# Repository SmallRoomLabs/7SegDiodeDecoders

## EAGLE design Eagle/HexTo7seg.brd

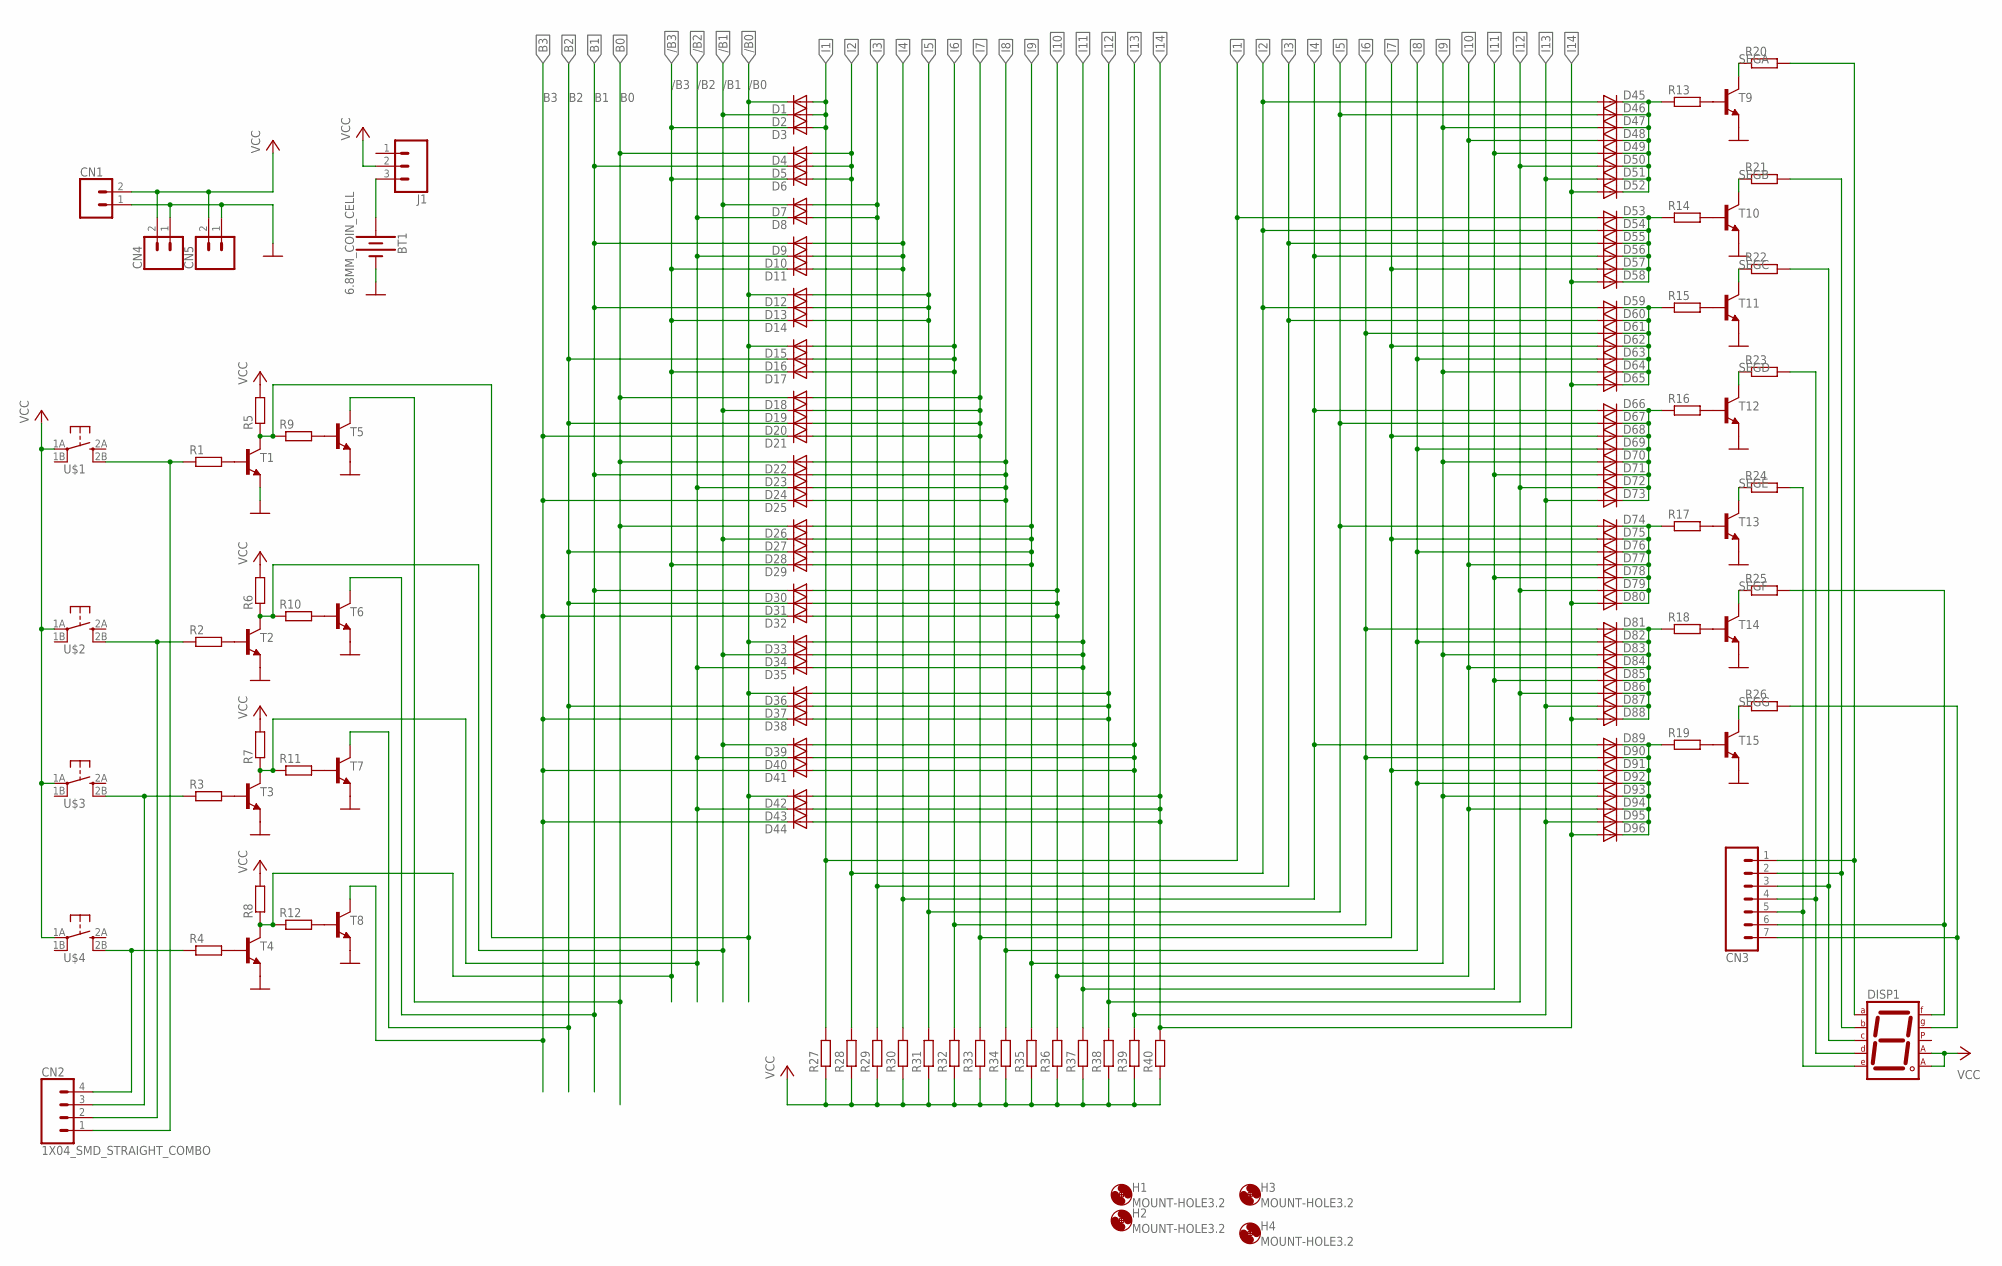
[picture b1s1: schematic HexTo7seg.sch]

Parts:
BT1: 6.8MM_COIN_CELL; BATTCOM_20MM_PTH
CN1, CN4, CN5: CONN_02; 1X02
CN2: 1X04_SMD_STRAIGHT_COMBO; 1X04
CN3: CONN_07; 1X07
D1, D2, D3, D4, D5, D6, D7, D8, D9, D10, D11, D12, D13, D14, D15, D16, D17, D18, D19, D20, D21, D22, D23, D24, D25, D26, D27, D28, D29, D30, D31, D32, D33, D34, D35, D36, D37, D38, D39, D40, D41, D42, D43, D44, D45, D46, D47, D48, D49, D50, D51, D52, D53, D54, D55, D56, D57, D58, D59, D60, D61, D62, D63, D64, D65, D66, D67, D68, D69, D70, D71, D72, D73, D74, D75, D76, D77, D78, D79, D80, D81, D82, D83, D84, D85, D86, D87, D88, D89, D90, D91, D92, D93, D94, D95, D96: SMALL_DIODEDO35-7; DO35-7
DISP1: 7SEG-CA; 7SEG-13
H1, H2, H3, H4: MOUNT-HOLE3.2; 3,2
J1: CONN_03NP; 1X03NOSTOP
R1, R2, R3, R4, R5, R6, R7, R8, R9, R10, R11, R12, R13, R14, R15, R16, R17, R18, R19, R20, R21, R22, R23, R24, R25, R26, R27, R28, R29, R30, R31, R32, R33, R34, R35, R36, R37, R38, R39, R40: RESISTOR7MM; 7MM_RESISTOR
T1, T2, T3, T4, T5, T6, T7, T8, T9, T10, T11, T12, T13, T14, T15: BC547B-NPN-TO92-CBE; TO92-CBE
U$1, U$2, U$3, U$4: TACTILETACT-6X6-PTH; TACTILE-PTH

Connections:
/B0: D1.C, D12.C, D15.C, D33.C, D36.C, D42.C, R5.1, R9.1, T1.C
/B1: D2.C, D7.C, D19.C, D27.C, D34.C, D39.C, R6.1, R10.1, T2.C
/B2: D8.C, D10.C, D24.C, D35.C, D40.C, D43.C, R7.1, R11.1, T3.C
/B3: D3.C, D6.C, D11.C, D14.C, D17.C, D29.C, R8.1, R12.1, T4.C
B0: D4.C, D18.C, D22.C, D26.C, T5.C
B1: D5.C, D9.C, D13.C, D23.C, D30.C, T6.C
B2: D16.C, D20.C, D28.C, D31.C, D37.C, T7.C
B3: D21.C, D25.C, D32.C, D38.C, D41.C, D44.C, T8.C
GND: BT1.2 (-), CN1.1, CN4.1, CN5.1, T1.E, T2.E, T3.E, T4.E, T5.E, T6.E, T7.E, T8.E, T9.E, T10.E, T11.E, T12.E, T13.E, T14.E, T15.E
I1: D1.A, D2.A, D3.A, D53.A, R27.2
I2: D4.A, D5.A, D6.A, D45.A, D54.A, D59.A, R28.2
I3: D7.A, D8.A, D55.A, D60.A, R29.2
I4: D9.A, D10.A, D11.A, D56.A, D66.A, D89.A, R30.2
I5: D12.A, D13.A, D14.A, D46.A, D67.A, D74.A, R31.2
I6: D15.A, D16.A, D17.A, D61.A, D81.A, D90.A, R32.2
I7: D18.A, D19.A, D20.A, D21.A, D57.A, D62.A, D68.A, D75.A, D91.A, R33.2
I8: D22.A, D23.A, D24.A, D25.A, D63.A, D69.A, D76.A, D82.A, D92.A, R34.2
I9: D26.A, D27.A, D28.A, D29.A, D47.A, D64.A, D70.A, D83.A, D93.A, R35.2
I10: D30.A, D31.A, D32.A, D48.A, D77.A, D84.A, D94.A, R36.2
I11: D33.A, D34.A, D35.A, D49.A, D71.A, D78.A, D85.A, R37.2
I12: D36.A, D37.A, D38.A, D50.A, D72.A, D79.A, D86.A, R38.2
I13: D39.A, D40.A, D41.A, D51.A, D73.A, D87.A, D95.A, R39.2
I14: D42.A, D43.A, D44.A, D52.A, D58.A, D65.A, D80.A, D88.A, D96.A, R40.2
IN0: CN2.1, R1.1, U$1.2B
IN1: CN2.2, R2.1, U$2.2B
IN2: CN2.3, R3.1, U$3.2B
IN3: CN2.4, R4.1, U$4.2B
unnamed: R13.2, T9.B
unnamed: CN3.1, DISP1.7 (A), R20.2
unnamed: R14.2, T10.B
unnamed: R15.2, T11.B
unnamed: R16.2, T12.B
unnamed: R17.2, T13.B
unnamed: R18.2, T14.B
unnamed: R19.2, T15.B
unnamed: CN3.2, DISP1.6 (B), R21.2
unnamed: CN3.3, DISP1.4 (C), R22.2
unnamed: CN3.4, DISP1.2 (D), R23.2
unnamed: CN3.5, DISP1.1 (E), R24.2
unnamed: CN3.6, DISP1.9 (F), R25.2
unnamed: CN3.7, DISP1.10 (G), R26.2
unnamed: BT1.1 (+), J1.3
unnamed: R1.2, T1.B
unnamed: R2.2, T2.B
unnamed: R3.2, T3.B
unnamed: R4.2, T4.B
unnamed: R12.2, T8.B
unnamed: R11.2, T7.B
unnamed: R10.2, T6.B
unnamed: R9.2, T5.B
ORA: D45.C, D46.C, D47.C, D48.C, D49.C, D50.C, D51.C, D52.C, R13.1
ORB: D53.C, D54.C, D55.C, D56.C, D57.C, D58.C, R14.1
ORC: D59.C, D60.C, D61.C, D62.C, D63.C, D64.C, D65.C, R15.1
ORD: D66.C, D67.C, D68.C, D69.C, D70.C, D71.C, D72.C, D73.C, R16.1
ORE: D74.C, D75.C, D76.C, D77.C, D78.C, D79.C, D80.C, R17.1
ORF: D81.C, D82.C, D83.C, D84.C, D85.C, D86.C, D87.C, D88.C, R18.1
ORG: D89.C, D90.C, D91.C, D92.C, D93.C, D94.C, D95.C, D96.C, R19.1
SEGA: R20.1, T9.C
SEGB: R21.1, T10.C
SEGC: R22.1, T11.C
SEGD: R23.1, T12.C
SEGE: R24.1, T13.C
SEGF: R25.1, T14.C
SEGG: R26.1, T15.C
VCC: CN1.2, CN4.2, CN5.2, DISP1.3 (CA1), DISP1.8 (CA2), J1.2, R5.2, R6.2, R7.2, R8.2, R27.1, R28.1, R29.1, R30.1, R31.1, R32.1, R33.1, R34.1, R35.1, R36.1, R37.1, R38.1, R39.1, R40.1, U$1.1A, U$2.1A, U$3.1A, U$4.1A

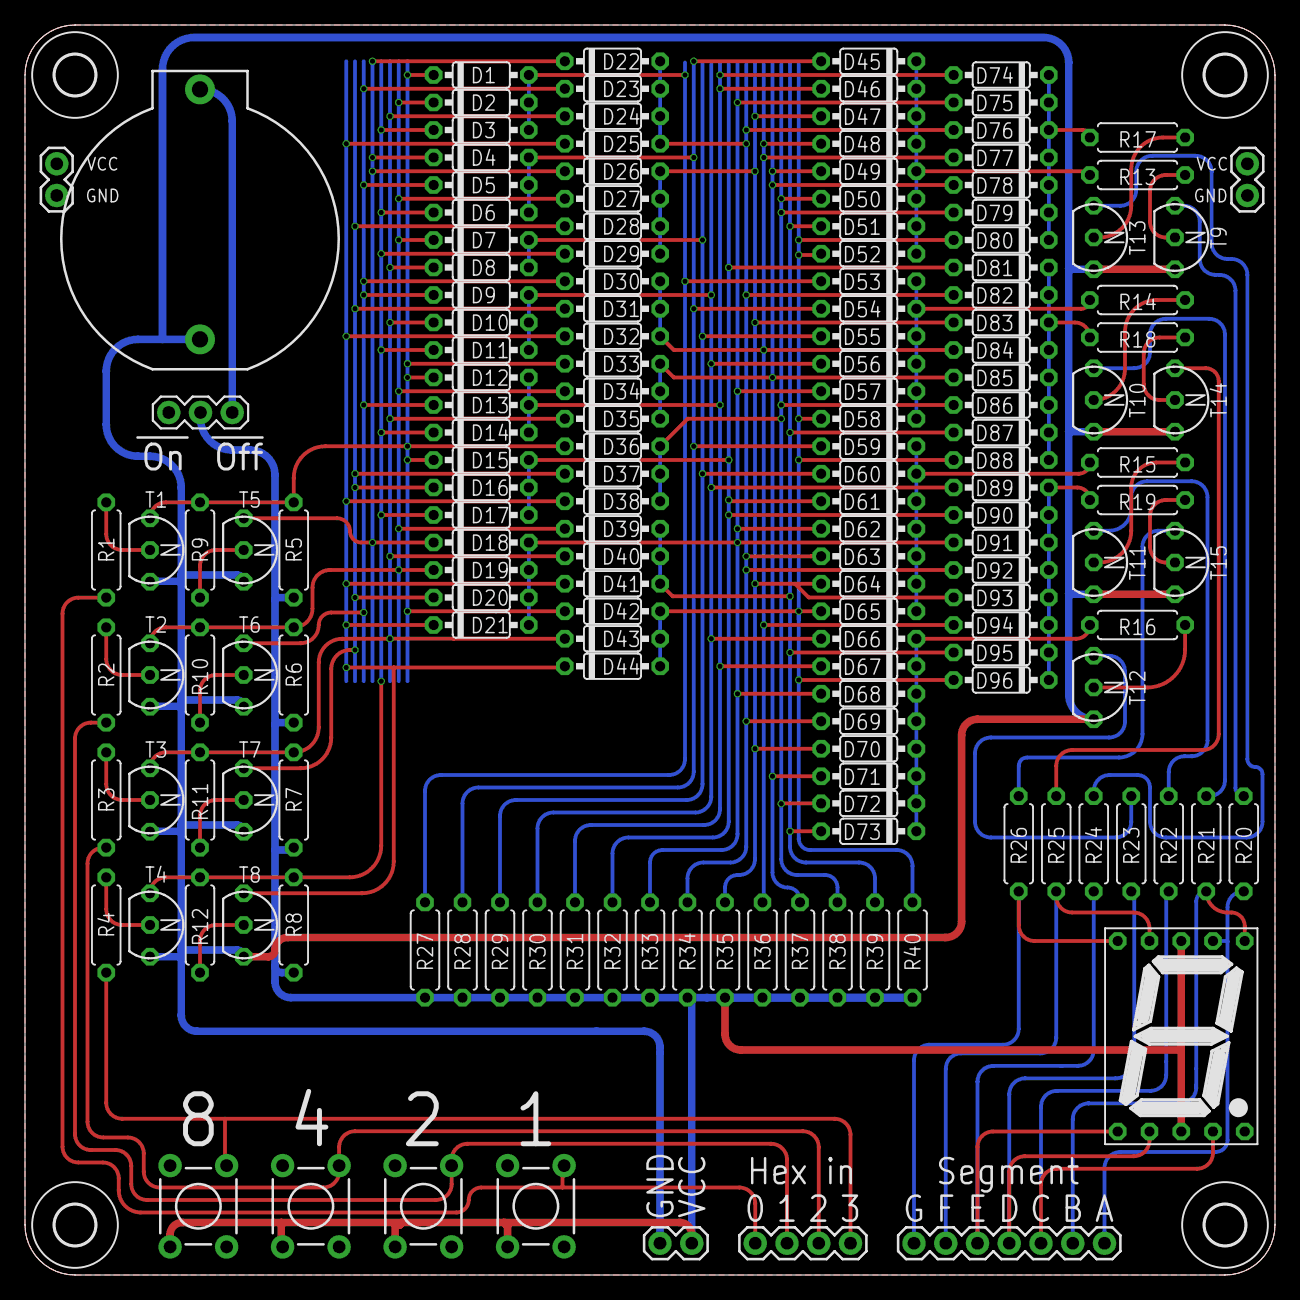
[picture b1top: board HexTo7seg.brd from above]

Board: 4 copper layers, 100.0 x 100.0 mm, 167 parts (0 on the bottom side), 65 nets.

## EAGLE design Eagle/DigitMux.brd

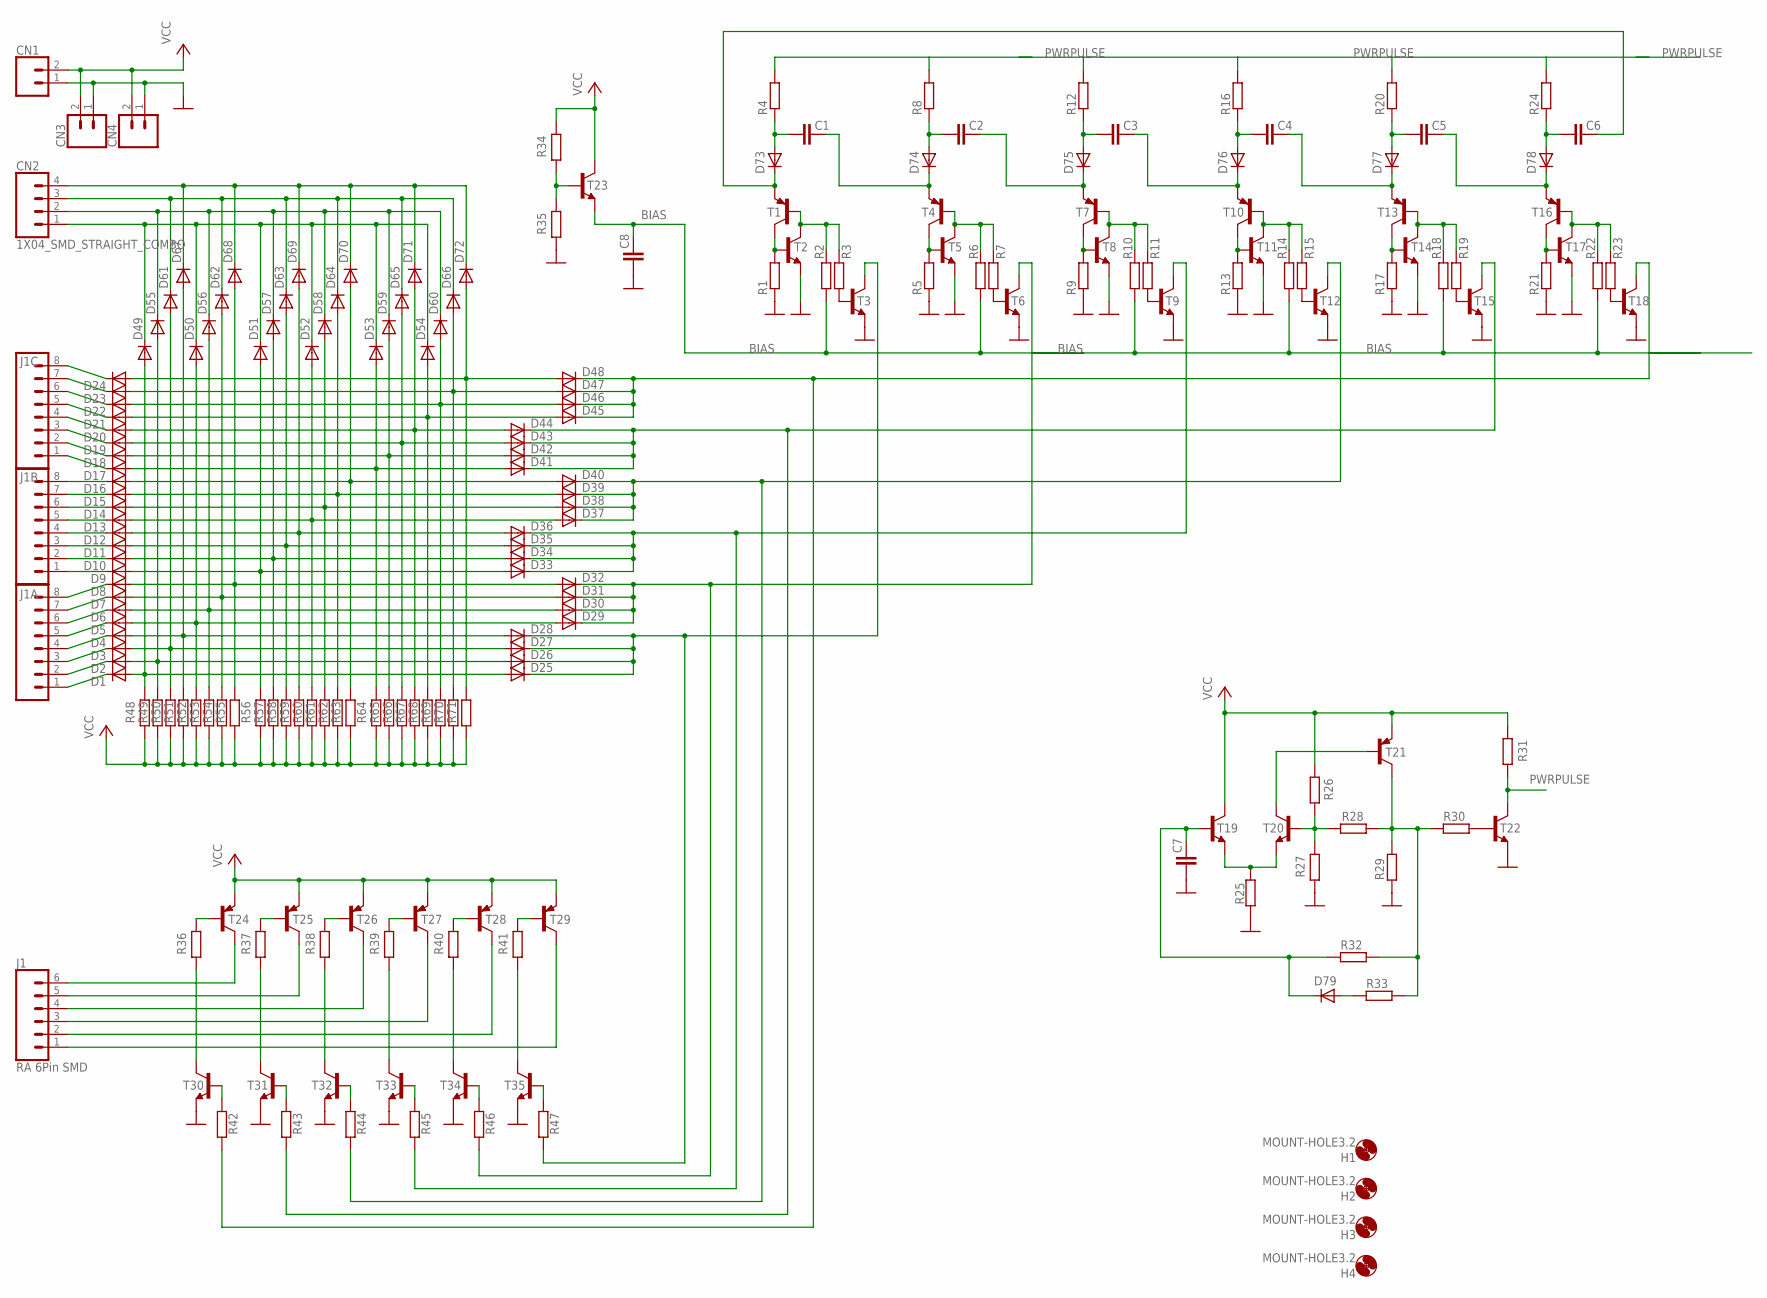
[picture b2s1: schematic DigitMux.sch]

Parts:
C1, C2, C3, C4, C5, C6, C7, C8: 0.1uF; CAP-PTH-SMALL-KIT
CN1, CN3, CN4: CONN_02; 1X02
CN2: 1X04_SMD_STRAIGHT_COMBO; 1X04
D1, D2, D3, D4, D5, D6, D7, D8, D9, D10, D11, D12, D13, D14, D15, D16, D17, D18, D19, D20, D21, D22, D23, D24, D25, D26, D27, D28, D29, D30, D31, D32, D33, D34, D35, D36, D37, D38, D39, D40, D41, D42, D43, D44, D45, D46, D47, D48, D49, D50, D51, D52, D53, D54, D55, D56, D57, D58, D59, D60, D61, D62, D63, D64, D65, D66, D67, D68, D69, D70, D71, D72, D73, D74, D75, D76, D77, D78, D79: SMALL_DIODEDO35-7; DO35-7
H1, H2, H3, H4: MOUNT-HOLE3.2; 3,2
J1: RA 6Pin SMD; 1X06
J1A, J1B, J1C: CONN_08"; 1X08
R1, R2, R3, R4, R5, R6, R7, R8, R9, R10, R11, R12, R13, R14, R15, R16, R17, R18, R19, R20, R21, R22, R23, R24, R25, R26, R27, R28, R29, R30, R31, R32, R33, R34, R35, R36, R37, R38, R39, R40, R41, R42, R43, R44, R45, R46, R47, R48, R49, R50, R51, R52, R53, R54, R55, R56, R57, R58, R59, R60, R61, R62, R63, R64, R65, R66, R67, R68, R69, R70, R71: RESISTOR7MM; 7MM_RESISTOR
T1, T4, T7, T10, T13, T16, T21, T24, T25, T26, T27, T28, T29: BC557B-PNP-TO92-EBC; TO92-EBC
T2, T3, T5, T6, T8, T9, T11, T12, T14, T15, T17, T18, T19, T20, T22, T23, T30, T31, T32, T33, T34, T35: BC547B-NPN-TO92-CBE; TO92-CBE

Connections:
BIAS: C8.2, R2.1, R6.1, R10.1, R14.1, R18.1, R22.1, T23.E
GND: C7.1, C8.1, CN1.1, CN3.1, CN4.1, R1.1, R5.1, R9.1, R13.1, R17.1, R21.1, R25.1, R27.1, R29.2, R35.1, T2.E, T3.E, T5.E, T6.E, T8.E, T9.E, T11.E, T12.E, T14.E, T15.E, T17.E, T18.E, T22.E, T30.E, T31.E, T32.E, T33.E, T34.E, T35.E
unnamed: R3.1, T3.B
unnamed: D1.C, J1A.1
unnamed: R1.2, T1.C, T2.B
unnamed: C6.2, D73.C, T1.E
unnamed: D37.C, D38.C, D39.C, D40.C, R44.1, T12.C
unnamed: D2.C, J1A.2
unnamed: D3.C, J1A.3
unnamed: D4.C, J1A.4
unnamed: D5.C, J1A.5
unnamed: D6.C, J1A.6
unnamed: D7.C, J1A.7
unnamed: D8.C, J1A.8
unnamed: D9.C, J1B.1
unnamed: D10.C, J1B.2
unnamed: D11.C, J1B.3
unnamed: D12.C, J1B.4
unnamed: D13.C, J1B.5
unnamed: D14.C, J1B.6
unnamed: D15.C, J1B.7
unnamed: D16.C, J1B.8
unnamed: D17.C, J1C.1
unnamed: D18.C, J1C.2
unnamed: D19.C, J1C.3
unnamed: D20.C, J1C.4
unnamed: D21.C, J1C.5
unnamed: D22.C, J1C.6
unnamed: D23.C, J1C.7
unnamed: D24.C, J1C.8
unnamed: D1.A, D25.A, D49.A, R48.2
unnamed: D17.A, D41.A, D53.A, R64.2
unnamed: D2.A, D26.A, D55.A, R49.2
unnamed: D3.A, D27.A, D61.A, R50.2
unnamed: D4.A, D28.A, D67.A, R51.2
unnamed: D5.A, D29.A, D50.A, R52.2
unnamed: D6.A, D30.A, D56.A, R53.2
unnamed: D7.A, D31.A, D62.A, R54.2
unnamed: D8.A, D32.A, D68.A, R55.2
unnamed: D9.A, D33.A, D51.A, R56.2
unnamed: D10.A, D34.A, D57.A, R57.2
unnamed: D11.A, D35.A, D63.A, R58.2
unnamed: D12.A, D36.A, D69.A, R59.2
unnamed: D13.A, D37.A, D52.A, R60.2
unnamed: D14.A, D38.A, D58.A, R61.2
unnamed: D15.A, D39.A, D64.A, R62.2
unnamed: D16.A, D40.A, D70.A, R63.2
unnamed: D18.A, D42.A, D59.A, R65.2
unnamed: D19.A, D43.A, D65.A, R66.2
unnamed: D20.A, D44.A, D71.A, R67.2
unnamed: D21.A, D45.A, D54.A, R68.2
unnamed: D22.A, D46.A, D60.A, R69.2
unnamed: D23.A, D47.A, D66.A, R70.2
unnamed: D24.A, D48.A, D72.A, R71.2
unnamed: R34.1, R35.2, T23.B
unnamed: R28.1, R29.1, R30.2, R32.1, R33.1, T21.C
unnamed: R11.1, T9.B
unnamed: D33.C, D34.C, D35.C, D36.C, R45.1, T9.C
unnamed: T20.C, T21.B
unnamed: D41.C, D42.C, D43.C, D44.C, R43.1, T15.C
unnamed: R2.2, R3.2, T1.B, T2.C
unnamed: CN2.1, D49.C, D50.C, D51.C, D52.C, D53.C, D54.C
unnamed: CN2.2, D55.C, D56.C, D57.C, D58.C, D59.C, D60.C
unnamed: CN2.3, D61.C, D62.C, D63.C, D64.C, D65.C, D66.C
unnamed: CN2.4, D67.C, D68.C, D69.C, D70.C, D71.C, D72.C
unnamed: C1.1, D73.A, R4.1
unnamed: R7.1, T6.B
unnamed: R5.2, T4.C, T5.B
unnamed: C1.2, D74.C, T4.E
unnamed: R25.2, T19.E, T20.E
unnamed: R9.2, T7.C, T8.B
unnamed: C2.1, D74.A, R8.1
unnamed: C2.2, D75.C, T7.E
unnamed: R19.1, T15.B
unnamed: R6.2, R7.2, T4.B, T5.C
unnamed: C3.1, D75.A, R12.1
unnamed: R15.1, T12.B
unnamed: R13.2, T10.C, T11.B
unnamed: R17.2, T13.C, T14.B
unnamed: R26.1, R27.2, R28.2, T20.B
unnamed: C4.1, D76.A, R16.1
unnamed: C4.2, D77.C, T13.E
unnamed: C3.2, D76.C, T10.E
unnamed: R10.2, R11.2, T7.B, T8.C
unnamed: R30.1, T22.B
unnamed: C5.1, D77.A, R20.1
unnamed: R23.1, T18.B
unnamed: R21.2, T16.C, T17.B
unnamed: C5.2, D78.C, T16.E
unnamed: J1.6, T24.C
unnamed: C6.1, D78.A, R24.1
unnamed: D79.A, R33.2
unnamed: C7.2, D79.C, R32.2, T19.B
unnamed: J1.5, T25.C
unnamed: J1.4, T26.C
unnamed: J1.3, T27.C
unnamed: J1.2, T28.C
unnamed: J1.1, T29.C
unnamed: R36.2, T24.B
unnamed: R37.2, T25.B
unnamed: R38.2, T26.B
unnamed: R39.2, T27.B
unnamed: R40.2, T28.B
unnamed: R41.2, T29.B
unnamed: R36.1, T30.C
unnamed: R37.1, T31.C
unnamed: R38.1, T32.C
unnamed: R39.1, T33.C
unnamed: R40.1, T34.C
unnamed: R41.1, T35.C
unnamed: D45.C, D46.C, D47.C, D48.C, R42.1, T18.C
unnamed: R42.2, T30.B
unnamed: R14.2, R15.2, T10.B, T11.C
unnamed: R43.2, T31.B
unnamed: R18.2, R19.2, T13.B, T14.C
unnamed: R44.2, T32.B
unnamed: R22.2, R23.2, T16.B, T17.C
unnamed: R45.2, T33.B
unnamed: D29.C, D30.C, D31.C, D32.C, R46.1, T6.C
unnamed: R46.2, T34.B
unnamed: D25.C, D26.C, D27.C, D28.C, R47.1, T3.C
unnamed: R47.2, T35.B
PWRPULSE: R4.2, R8.2, R12.2, R16.2, R20.2, R24.2, R31.1, T22.C
VCC: CN1.2, CN3.2, CN4.2, R26.2, R31.2, R34.2, R48.1, R49.1, R50.1, R51.1, R52.1, R53.1, R54.1, R55.1, R56.1, R57.1, R58.1, R59.1, R60.1, R61.1, R62.1, R63.1, R64.1, R65.1, R66.1, R67.1, R68.1, R69.1, R70.1, R71.1, T19.C, T21.E, T23.C, T24.E, T25.E, T26.E, T27.E, T28.E, T29.E

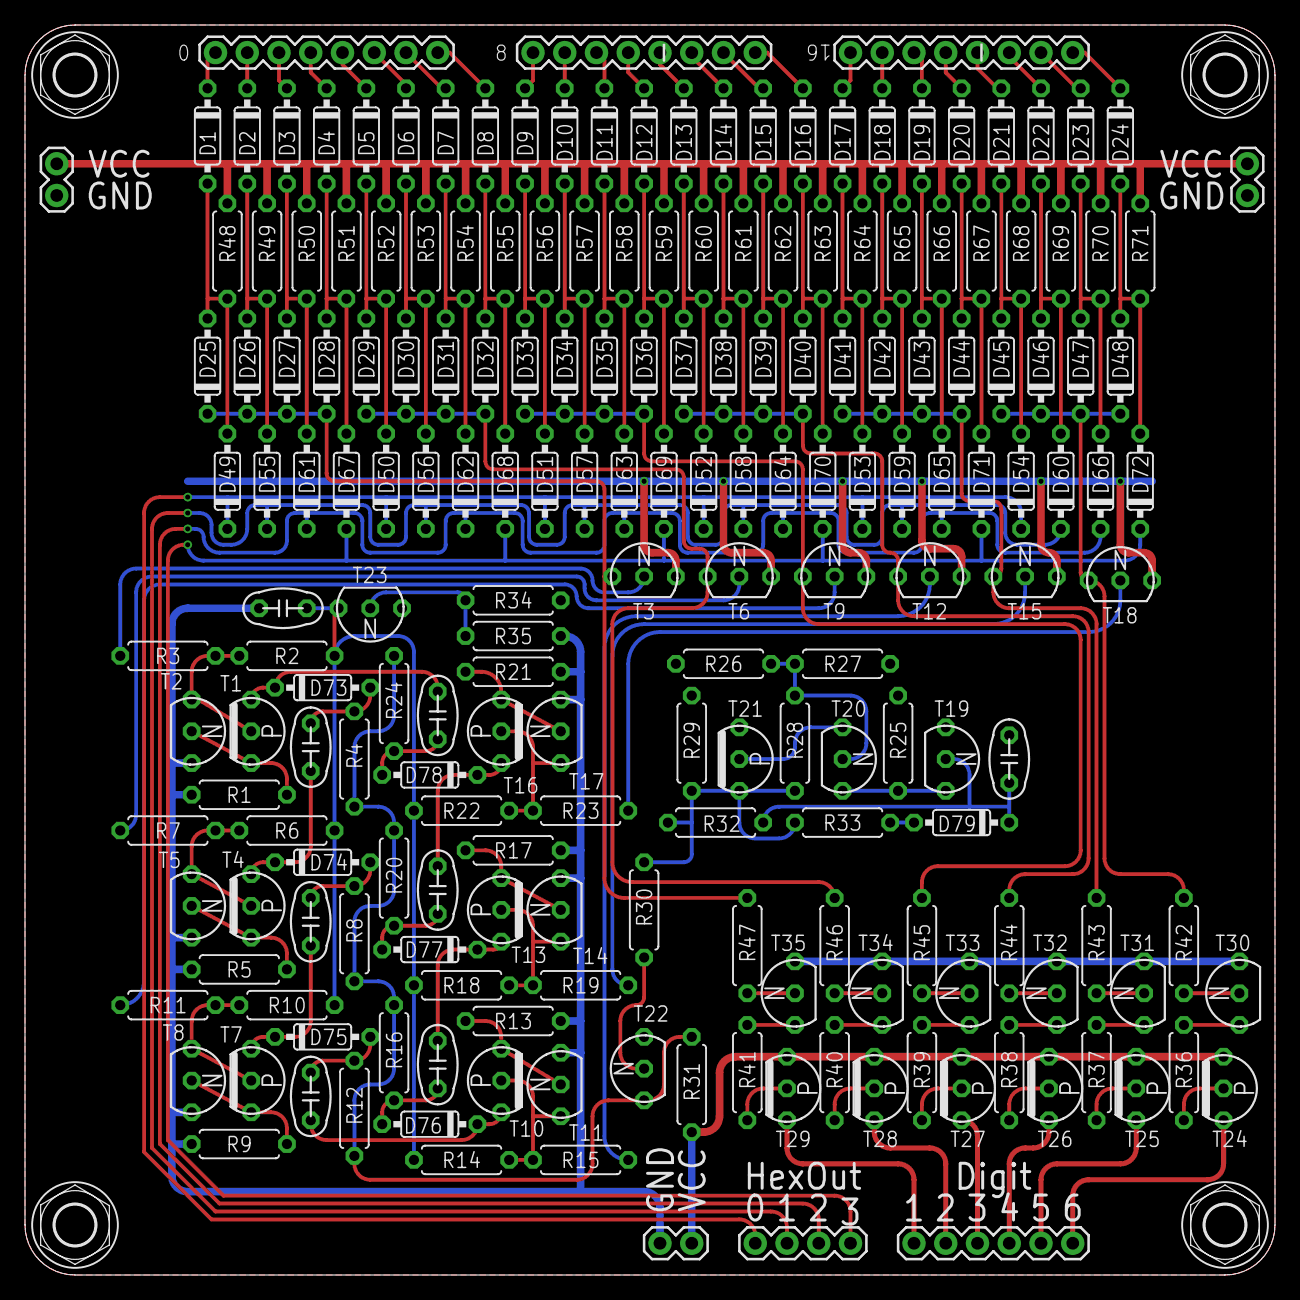
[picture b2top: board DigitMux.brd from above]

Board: 2 copper layers, 100.0 x 100.0 mm, 205 parts (0 on the bottom side), 124 nets.

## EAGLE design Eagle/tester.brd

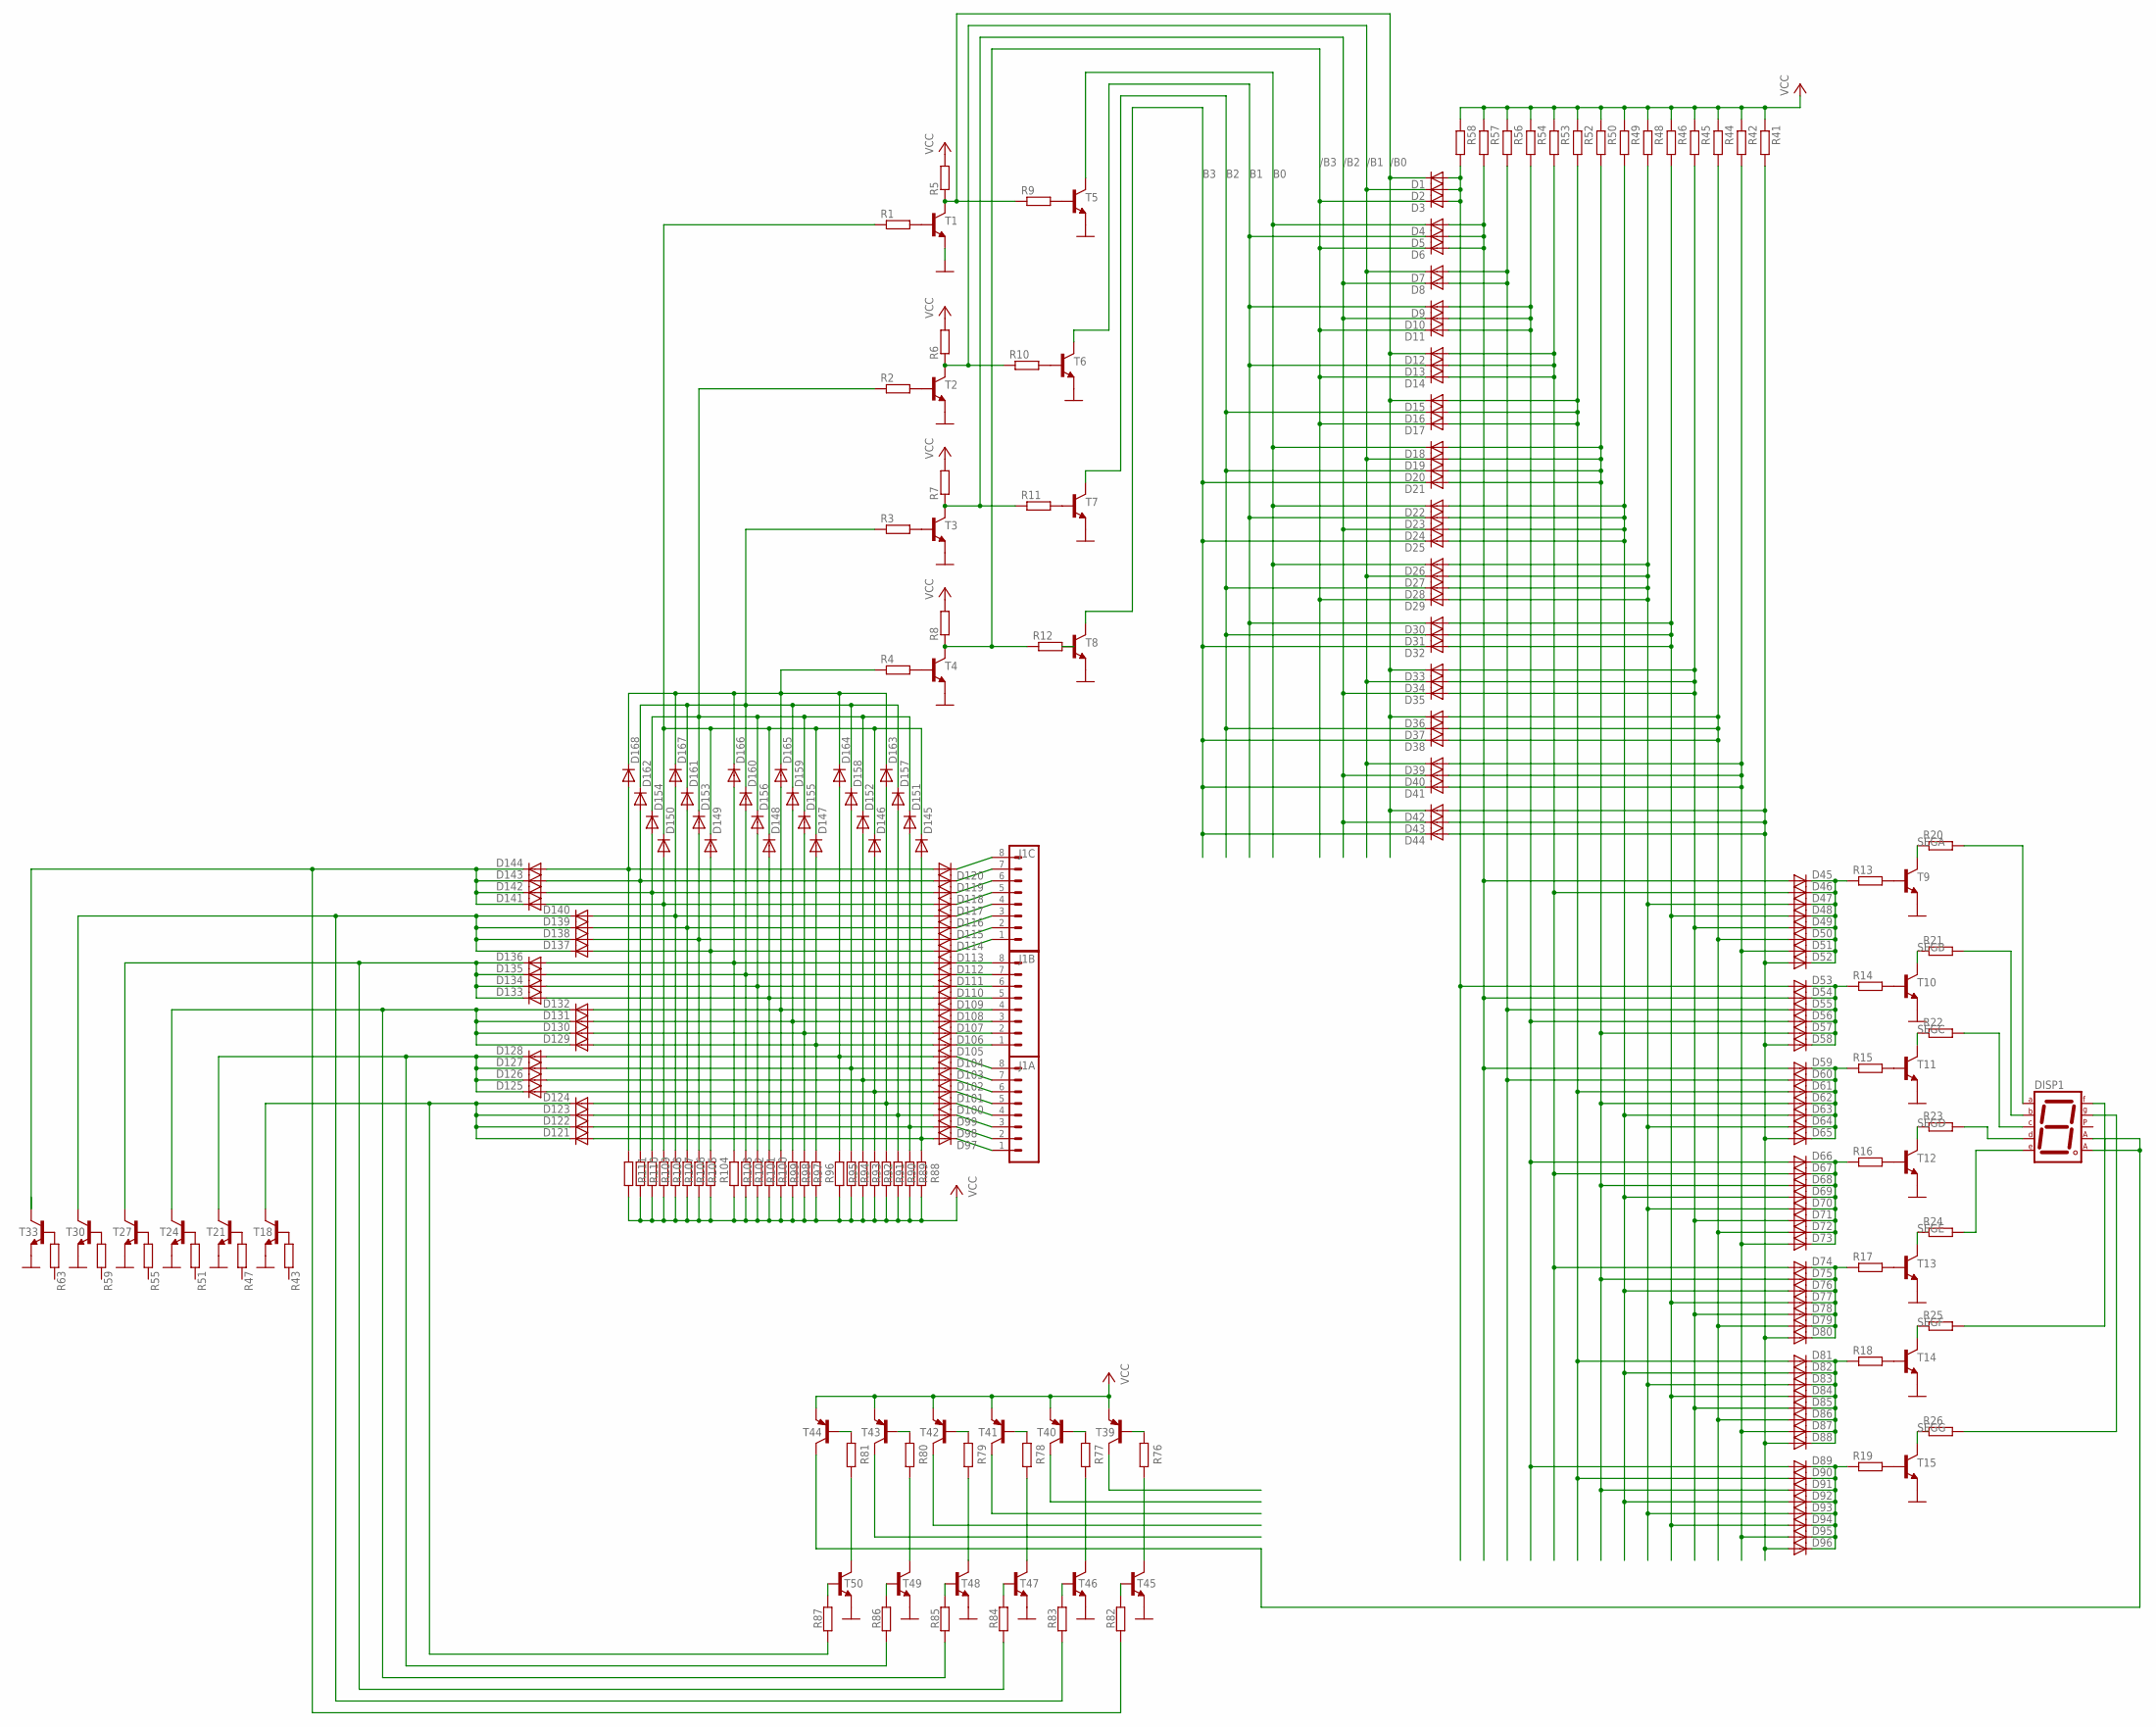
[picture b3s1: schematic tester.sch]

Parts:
D1, D2, D3, D4, D5, D6, D7, D8, D9, D10, D11, D12, D13, D14, D15, D16, D17, D18, D19, D20, D21, D22, D23, D24, D25, D26, D27, D28, D29, D30, D31, D32, D33, D34, D35, D36, D37, D38, D39, D40, D41, D42, D43, D44, D45, D46, D47, D48, D49, D50, D51, D52, D53, D54, D55, D56, D57, D58, D59, D60, D61, D62, D63, D64, D65, D66, D67, D68, D69, D70, D71, D72, D73, D74, D75, D76, D77, D78, D79, D80, D81, D82, D83, D84, D85, D86, D87, D88, D89, D90, D91, D92, D93, D94, D95, D96, D97, D98, D99, D100, D101, D102, D103, D104, D105, D106, D107, D108, D109, D110, D111, D112, D113, D114, D115, D116, D117, D118, D119, D120, D121, D122, D123, D124, D125, D126, D127, D128, D129, D130, D131, D132, D133, D134, D135, D136, D137, D138, D139, D140, D141, D142, D143, D144, D145, D146, D147, D148, D149, D150, D151, D152, D153, D154, D155, D156, D157, D158, D159, D160, D161, D162, D163, D164, D165, D166, D167, D168: SMALL_DIODEDO35-7; DO35-7
DISP1: 7SEG-CA; 7SEG-13
J1A, J1B, J1C: CONN_08"; 1X08
R1, R2, R3, R4, R5, R6, R7, R8, R9, R10, R11, R12, R13, R14, R15, R16, R17, R18, R19, R20, R21, R22, R23, R24, R25, R26, R41, R42, R43, R44, R45, R46, R47, R48, R49, R50, R51, R52, R53, R54, R55, R56, R57, R58, R59, R63, R76, R77, R78, R79, R80, R81, R82, R83, R84, R85, R86, R87, R88, R89, R90, R91, R92, R93, R94, R95, R96, R97, R98, R99, R100, R101, R102, R103, R104, R105, R106, R107, R108, R109, R110, R111: RESISTOR7MM; 7MM_RESISTOR
T1, T2, T3, T4, T5, T6, T7, T8, T9, T10, T11, T12, T13, T14, T15, T18, T21, T24, T27, T30, T33, T45, T46, T47, T48, T49, T50: BC547B-NPN-TO92-CBE; TO92-CBE
T39, T40, T41, T42, T43, T44: BC557B-PNP-TO92-EBC; TO92-EBC

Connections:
/B0: D1.C, D12.C, D15.C, D33.C, D36.C, D42.C, R5.1, R9.1, T1.C
/B1: D2.C, D7.C, D19.C, D27.C, D34.C, D39.C, R6.1, R10.1, T2.C
/B2: D8.C, D10.C, D24.C, D35.C, D40.C, D43.C, R7.1, R11.1, T3.C
/B3: D3.C, D6.C, D11.C, D14.C, D17.C, D29.C, R8.1, R12.1, T4.C
B0: D4.C, D18.C, D22.C, D26.C, T5.C
B1: D5.C, D9.C, D13.C, D23.C, D30.C, T6.C
B2: D16.C, D20.C, D28.C, D31.C, D37.C, T7.C
B3: D21.C, D25.C, D32.C, D38.C, D41.C, D44.C, T8.C
GND: T1.E, T2.E, T3.E, T4.E, T5.E, T6.E, T7.E, T8.E, T9.E, T10.E, T11.E, T12.E, T13.E, T14.E, T15.E, T18.E, T21.E, T24.E, T27.E, T30.E, T33.E, T45.E, T46.E, T47.E, T48.E, T49.E, T50.E
I9: D26.A, D27.A, D28.A, D29.A, D47.A, D64.A, D70.A, D83.A, D93.A, R48.2
I10: D30.A, D31.A, D32.A, D48.A, D77.A, D84.A, D94.A, R46.2
I11: D33.A, D34.A, D35.A, D49.A, D71.A, D78.A, D85.A, R45.2
I12: D36.A, D37.A, D38.A, D50.A, D72.A, D79.A, D86.A, R44.2
I13: D39.A, D40.A, D41.A, D51.A, D73.A, D87.A, D95.A, R42.2
I14: D42.A, D43.A, D44.A, D52.A, D58.A, D65.A, D80.A, D88.A, D96.A, R41.2
IN0: D145.C, D146.C, D147.C, D148.C, D149.C, D150.C, R1.1
IN1: D151.C, D152.C, D153.C, D154.C, D155.C, D156.C, R2.1
IN2: D157.C, D158.C, D159.C, D160.C, D161.C, D162.C, R3.1
IN3: D163.C, D164.C, D165.C, D166.C, D167.C, D168.C, R4.1
unnamed: R13.2, T9.B
unnamed: DISP1.7 (A), R20.2
unnamed: R14.2, T10.B
unnamed: R15.2, T11.B
unnamed: R16.2, T12.B
unnamed: R17.2, T13.B
unnamed: R18.2, T14.B
unnamed: R19.2, T15.B
unnamed: DISP1.6 (B), R21.2
unnamed: DISP1.4 (C), R22.2
unnamed: DISP1.2 (D), R23.2
unnamed: DISP1.1 (E), R24.2
unnamed: DISP1.9 (F), R25.2
unnamed: DISP1.10 (G), R26.2
unnamed: D97.C, J1A.1
unnamed: D1.A, D2.A, D3.A, D53.A, R58.2
unnamed: D98.C, J1A.2
unnamed: D99.C, J1A.3
unnamed: D100.C, J1A.4
unnamed: D101.C, J1A.5
unnamed: D102.C, J1A.6
unnamed: R1.2, T1.B
unnamed: R2.2, T2.B
unnamed: R3.2, T3.B
unnamed: R4.2, T4.B
unnamed: R12.2, T8.B
unnamed: R11.2, T7.B
unnamed: R10.2, T6.B
unnamed: R9.2, T5.B
unnamed: D103.C, J1A.7
unnamed: D104.C, J1A.8
unnamed: D105.C, J1B.1
unnamed: D106.C, J1B.2
unnamed: D107.C, J1B.3
unnamed: D108.C, J1B.4
unnamed: D109.C, J1B.5
unnamed: D110.C, J1B.6
unnamed: D111.C, J1B.7
unnamed: D112.C, J1B.8
unnamed: D113.C, J1C.1
unnamed: D114.C, J1C.2
unnamed: D115.C, J1C.3
unnamed: D116.C, J1C.4
unnamed: D117.C, J1C.5
unnamed: D118.C, J1C.6
unnamed: D119.C, J1C.7
unnamed: D120.C, J1C.8
unnamed: D97.A, D121.A, D145.A, R88.2
unnamed: D99.A, D123.A, D157.A, R90.2
unnamed: D100.A, D124.A, D163.A, R91.2
unnamed: D101.A, D125.A, D146.A, R92.2
unnamed: D102.A, D126.A, D152.A, R93.2
unnamed: D103.A, D127.A, D158.A, R94.2
unnamed: D104.A, D128.A, D164.A, R95.2
unnamed: D105.A, D129.A, D147.A, R96.2
unnamed: D106.A, D130.A, D155.A, R97.2
unnamed: D107.A, D131.A, D159.A, R98.2
unnamed: D108.A, D132.A, D165.A, R99.2
unnamed: D109.A, D133.A, D148.A, R100.2
unnamed: D110.A, D134.A, D156.A, R101.2
unnamed: D111.A, D135.A, D160.A, R102.2
unnamed: D112.A, D136.A, D166.A, R103.2
unnamed: D113.A, D137.A, D149.A, R104.2
unnamed: D114.A, D138.A, D153.A, R105.2
unnamed: D115.A, D139.A, D161.A, R106.2
unnamed: D116.A, D140.A, D167.A, R107.2
unnamed: D117.A, D141.A, D150.A, R108.2
unnamed: D118.A, D142.A, D154.A, R109.2
unnamed: D119.A, D143.A, D162.A, R110.2
unnamed: D120.A, D144.A, D168.A, R111.2
unnamed: D129.C, D130.C, D131.C, D132.C, R85.1, T24.C
unnamed: D137.C, D138.C, D139.C, D140.C, R83.1, T30.C
unnamed: D98.A, D122.A, D151.A, R89.2
unnamed: R43.1, T18.B
unnamed: D4.A, D5.A, D6.A, D45.A, D54.A, D59.A, R57.2
unnamed: D7.A, D8.A, D55.A, D60.A, R56.2
unnamed: D9.A, D10.A, D11.A, D56.A, D66.A, D89.A, R54.2
unnamed: R47.1, T21.B
unnamed: D12.A, D13.A, D14.A, D46.A, D67.A, D74.A, R53.2
unnamed: D15.A, D16.A, D17.A, D61.A, D81.A, D90.A, R52.2
unnamed: D18.A, D19.A, D20.A, D21.A, D57.A, D62.A, D68.A, D75.A, D91.A, R50.2
unnamed: R51.1, T24.B
unnamed: D22.A, D23.A, D24.A, D25.A, D63.A, D69.A, D76.A, D82.A, D92.A, R49.2
unnamed: DISP1.3 (CA1), DISP1.8 (CA2), T44.C
unnamed: R55.1, T27.B
unnamed: R59.1, T30.B
unnamed: R63.1, T33.B
unnamed: R76.2, T39.B
unnamed: R77.2, T40.B
unnamed: R78.2, T41.B
unnamed: R79.2, T42.B
unnamed: R80.2, T43.B
unnamed: R81.2, T44.B
unnamed: R76.1, T45.C
unnamed: R77.1, T46.C
unnamed: R78.1, T47.C
unnamed: R79.1, T48.C
unnamed: R80.1, T49.C
unnamed: R81.1, T50.C
unnamed: D141.C, D142.C, D143.C, D144.C, R82.1, T33.C
unnamed: R82.2, T45.B
unnamed: R83.2, T46.B
unnamed: R84.2, T47.B
unnamed: R85.2, T48.B
unnamed: D125.C, D126.C, D127.C, D128.C, R86.1, T21.C
unnamed: R86.2, T49.B
unnamed: D121.C, D122.C, D123.C, D124.C, R87.1, T18.C
unnamed: R87.2, T50.B
unnamed: D133.C, D134.C, D135.C, D136.C, R84.1, T27.C
ORA: D45.C, D46.C, D47.C, D48.C, D49.C, D50.C, D51.C, D52.C, R13.1
ORB: D53.C, D54.C, D55.C, D56.C, D57.C, D58.C, R14.1
ORC: D59.C, D60.C, D61.C, D62.C, D63.C, D64.C, D65.C, R15.1
ORD: D66.C, D67.C, D68.C, D69.C, D70.C, D71.C, D72.C, D73.C, R16.1
ORE: D74.C, D75.C, D76.C, D77.C, D78.C, D79.C, D80.C, R17.1
ORF: D81.C, D82.C, D83.C, D84.C, D85.C, D86.C, D87.C, D88.C, R18.1
ORG: D89.C, D90.C, D91.C, D92.C, D93.C, D94.C, D95.C, D96.C, R19.1
SEGA: R20.1, T9.C
SEGB: R21.1, T10.C
SEGC: R22.1, T11.C
SEGD: R23.1, T12.C
SEGE: R24.1, T13.C
SEGF: R25.1, T14.C
SEGG: R26.1, T15.C
VCC: R5.2, R6.2, R7.2, R8.2, R41.1, R42.1, R44.1, R45.1, R46.1, R48.1, R49.1, R50.1, R52.1, R53.1, R54.1, R56.1, R57.1, R58.1, R88.1, R89.1, R90.1, R91.1, R92.1, R93.1, R94.1, R95.1, R96.1, R97.1, R98.1, R99.1, R100.1, R101.1, R102.1, R103.1, R104.1, R105.1, R106.1, R107.1, R108.1, R109.1, R110.1, R111.1, T39.E, T40.E, T41.E, T42.E, T43.E, T44.E
